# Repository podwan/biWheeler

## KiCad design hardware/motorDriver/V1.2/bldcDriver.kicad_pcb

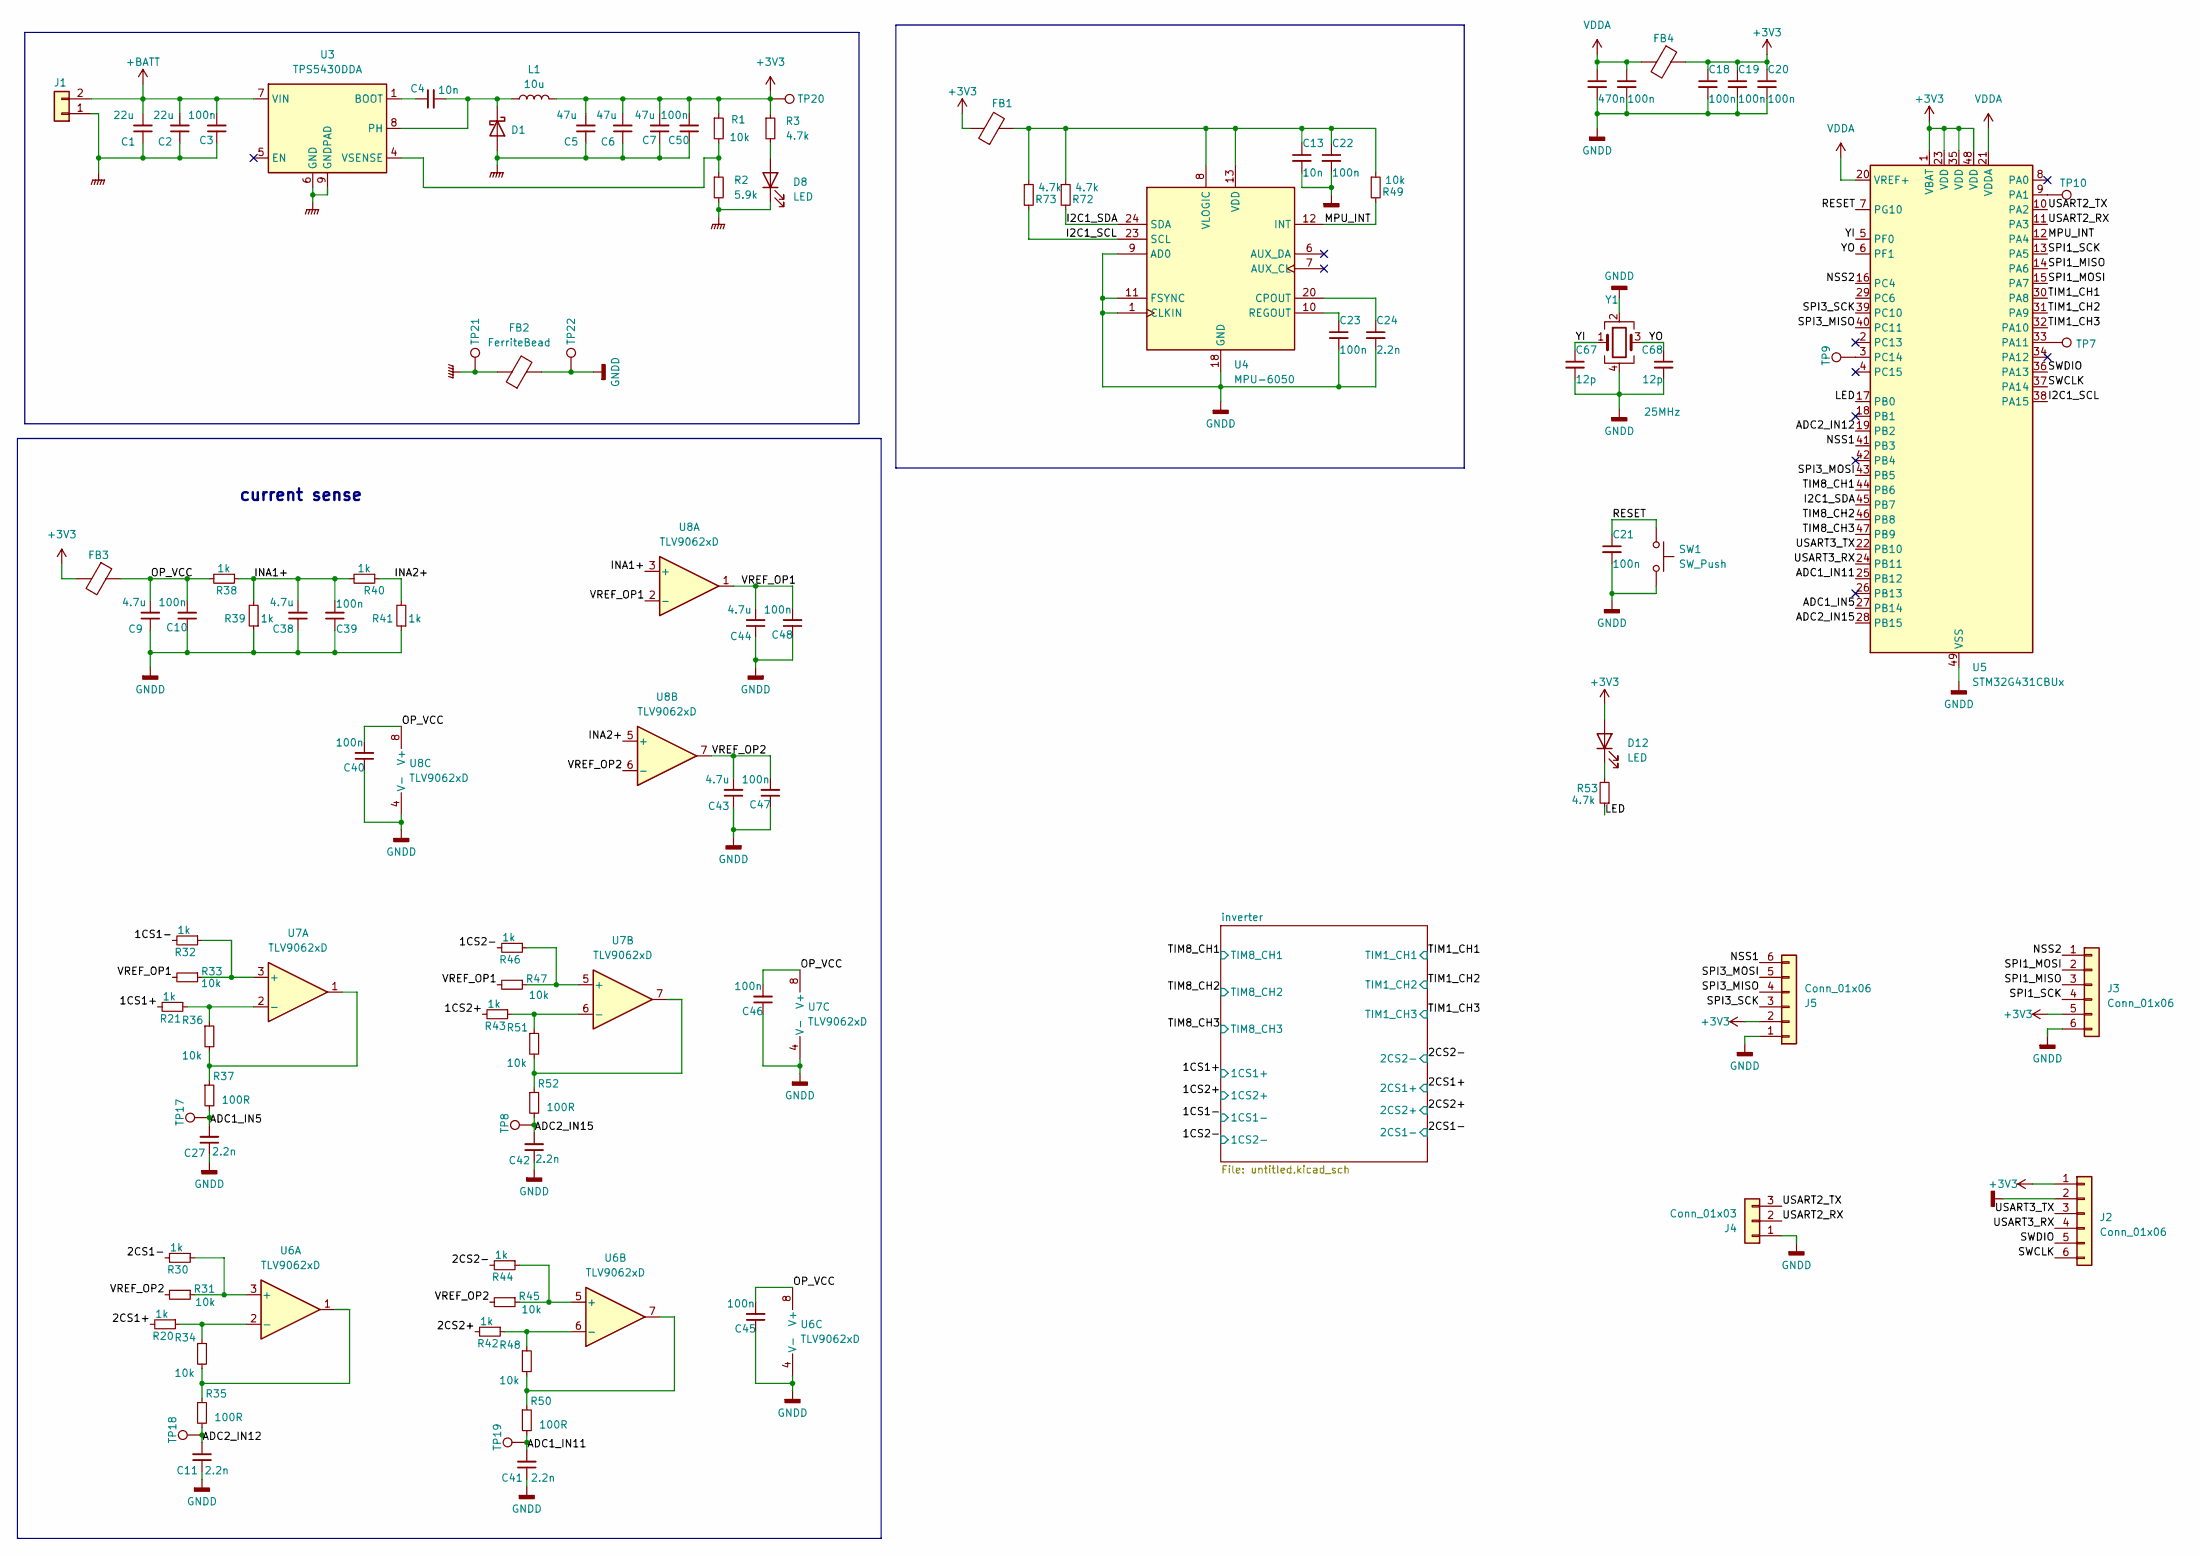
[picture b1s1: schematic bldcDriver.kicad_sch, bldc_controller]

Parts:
C1, C2: 22u; C_0805_2012Metric_Pad1.18x1.45mm_HandSolder
C3, C10, C17, C18, C19, C20, C21, C22, C23, C39, C40, C45, C46, C47, C48, C50: 100n; C_0603_1608Metric_Pad1.08x0.95mm_HandSolder
C4, C13: 10n; C_0603_1608Metric_Pad1.08x0.95mm_HandSolder
C5, C6, C7: 47u; C_1206_3216Metric_Pad1.33x1.80mm_HandSolder
C8: 470n; C_0603_1608Metric_Pad1.08x0.95mm_HandSolder
C9, C38, C43, C44: 4.7u; C_0603_1608Metric_Pad1.08x0.95mm_HandSolder
C11, C24, C27, C41, C42: 2.2n; C_0603_1608Metric_Pad1.08x0.95mm_HandSolder
C67, C68: 12p; C_0603_1608Metric_Pad1.08x0.95mm_HandSolder
D1: 1N5712UR; SMA_L4.3-W2.6-LS5.0-RD
D8: LED; LED_0603_1608Metric_Pad1.05x0.95mm_HandSolder
D12: LED; LED_0805_2012Metric_Pad1.15x1.40mm_HandSolder
FB1, FB3, FB4: FerriteBead; C_0603_1608Metric_Pad1.08x0.95mm_HandSolder
FB2: FerriteBead; R_1206_3216Metric_Pad1.30x1.75mm_HandSolder
J1: Conn_01x02; AMASS_XT30U-M_1x02_P5.0mm_Vertical
J2, J3, J5: Conn_01x06; CONN-SMD_6P-P1.00_MEGASTAR_ZX-SH1.0-6PWT
J4: Conn_01x03; CONN-SMD_3P-P1.00_WAFER-SH1.0-3PWB
L1: 10u; L_Taiyo-Yuden_NR-40xx_HandSoldering
R1, R31, R33, R34, R36, R45, R47, R48, R49, R51: 10k; R_0603_1608Metric_Pad0.98x0.95mm_HandSolder
R2: 5.9k; R_0603_1608Metric_Pad0.98x0.95mm_HandSolder
R3, R53, R72, R73: 4.7k; R_0603_1608Metric_Pad0.98x0.95mm_HandSolder
R20, R21, R30, R32, R38, R39, R40, R41, R42, R43, R44, R46: 1k; R_0603_1608Metric_Pad0.98x0.95mm_HandSolder
R35, R37, R50, R52: 100R; R_0603_1608Metric_Pad0.98x0.95mm_HandSolder
SW1: SW_Push; SW_SPST_B3U-1000P
TP7, TP8, TP9, TP10, TP17, TP18, TP19, TP20, TP21, TP22: TestPoint; TestPoint_Pad_D1.0mm
U3: TPS5430DDA; TI_SO-PowerPAD-8_ThermalVias
U4: MPU-6050; InvenSense_QFN-24_4x4mm_P0.5mm
U5: STM32G431CBUx; QFN-48-1EP_7x7mm_P0.5mm_EP5.6x5.6mm
U6, U7, U8: TLV9062xD; SOIC-8_3.9x4.9mm_P1.27mm
Y1: 25MHz; Crystal_SMD_SeikoEpson_FA238-4Pin_3.2x2.5mm

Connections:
+3V3: C5.2, C6.2, C7.2, C18.1, C19.1, C20.1, C50.2, D12.2 (A), FB1.1, FB3.2, FB4.1, J2.1, J3.5, J5.2, L1.2, R1.1, R3.1, TP20.1, U5.1 (VBAT), U5.23 (VDD), U5.35 (VDD), U5.48 (VDD)
+BATT: C1.2, C2.2, C3.2, J1.2, U3.7 (VIN); also elsewhere on the board
/1CS1+: R21.2; also elsewhere on the board
/1CS1-: R32.2; also elsewhere on the board
/1CS2+: R43.2; also elsewhere on the board
/1CS2-: R46.2; also elsewhere on the board
/2CS1+: R20.2; also elsewhere on the board
/2CS1-: R30.2; also elsewhere on the board
/2CS2+: R42.2; also elsewhere on the board
/2CS2-: R44.2; also elsewhere on the board
/ADC1_IN5: C27.2, R37.2, TP17.1, U5.27 (PB14)
/ADC1_IN11: C41.2, R50.2, TP19.1, U5.25 (PB12)
/ADC2_IN12: C11.2, R35.2, TP18.1, U5.19 (PB2)
/ADC2_IN15: C42.2, R52.2, TP8.1, U5.28 (PB15)
/I2C1_SCL: R73.2, U4.23 (SCL), U5.38 (PA15)
/I2C1_SDA: R72.2, U4.24 (SDA), U5.45 (PB7)
/INA1+: C38.2, C39.2, R38.1, R39.2, R40.2, U8.3 (+)
/INA2+: R40.1, R41.2, U8.5 (+)
/LED: R53.1, U5.17 (PB0)
/MPU_INT: R49.2, U4.12 (INT), U5.12 (PA4)
/NSS1: J5.6, U5.41 (PB3)
/NSS2: J3.1, U5.16 (PC4)
/OP_VCC: C9.2, C10.2, C40.2, C45.2, C46.2, FB3.1, R38.2, U6.8 (V+), U7.8 (V+), U8.8 (V+)
/RESET: C21.1, SW1.1, U5.7 (PG10)
/SPI1_MISO: J3.3, U5.14 (PA6)
/SPI1_MOSI: J3.2, U5.15 (PA7)
/SPI1_SCK: J3.4, U5.13 (PA5)
/SPI3_MISO: J5.4, U5.40 (PC11)
/SPI3_MOSI: J5.5, U5.43 (PB5)
/SPI3_SCK: J5.3, U5.39 (PC10)
/SWCLK: J2.6, U5.37 (PA14)
/SWDIO: J2.5, U5.36 (PA13)
/TIM1_CH1: U5.30 (PA8); also elsewhere on the board
/TIM1_CH2: U5.31 (PA9); also elsewhere on the board
/TIM1_CH3: U5.32 (PA10); also elsewhere on the board
/TIM8_CH1: U5.44 (PB6); also elsewhere on the board
/TIM8_CH2: U5.46 (PB8); also elsewhere on the board
/TIM8_CH3: U5.47 (PB9); also elsewhere on the board
/USART2_RX: J4.2, U5.11 (PA3)
/USART2_TX: J4.3, U5.10 (PA2)
/USART3_RX: J2.4, U5.24 (PB11)
/USART3_TX: J2.3, U5.22 (PB10)
/VREF_OP1: C44.2, C48.2, R33.2, R47.2, U8.1, U8.2 (-)
/VREF_OP2: C43.2, C47.2, R31.2, R45.2, U8.6 (-), U8.7
/YI: C67.1, U5.5 (PF0), Y1.1
/YO: C68.1, U5.6 (PF1), Y1.3
GNDD: C8.2, C9.1, C10.1, C11.1, C13.2, C17.2, C18.2, C19.2, C20.2, C21.2, C22.2, C23.2, C24.2, C27.1, C38.1, C39.1, C40.1, C41.1, C42.1, C43.1, C44.1, C45.1, C46.1, C47.1, C48.1, C67.2, C68.2, FB2.2, J2.2, J3.6, J4.1, J5.1, R39.1, R41.1, SW1.2, TP22.1, U4.1 (CLKIN), U4.9 (AD0), U4.11 (FSYNC), U4.18 (GND), U5.49 (VSS), U6.4 (V-), U7.4 (V-), U8.4 (V-), Y1.2, Y1.4
GNDPWR: C1.1, C2.1, C3.1, C5.1, C6.1, C7.1, C50.1, D1.2 (A), D8.1 (K), FB2.1, J1.1, R2.2, TP21.1, U3.6 (GND), U3.9 (GNDPAD); also elsewhere on the board
unnamed: C4.2, D1.1 (K), L1.1, U3.8 (PH)
unnamed: D8.2 (A), R3.2
unnamed: D12.1 (K), R53.2
unnamed: R34.2, R35.1, U6.1
unnamed: R36.2, R37.1, U7.1
unnamed: R48.2, R50.1, U6.7
unnamed: R51.2, R52.1, U7.7
unnamed: C4.1, U3.1 (BOOT)
unnamed: R1.2, R2.1, U3.4 (VSENSE)
unnamed: C24.1, U4.20 (CPOUT)
unnamed: C23.1, U4.10 (REGOUT)
unnamed: C13.1, C22.1, FB1.2, R49.1, R72.1, R73.1, U4.8 (VLOGIC), U4.13 (VDD)
unnamed: TP10.1, U5.9 (PA1)
unnamed: TP7.1, U5.33 (PA11)
unnamed: TP9.1, U5.3 (PC14)
unnamed: R30.1, R31.1, U6.3 (+)
unnamed: R20.1, R34.1, U6.2 (-)
unnamed: R44.1, R45.1, U6.5 (+)
unnamed: R42.1, R48.1, U6.6 (-)
unnamed: R32.1, R33.1, U7.3 (+)
unnamed: R21.1, R36.1, U7.2 (-)
unnamed: R46.1, R47.1, U7.5 (+)
unnamed: R43.1, R51.1, U7.6 (-)
VDDA: C8.1, C17.1, FB4.2, U5.20 (VREF+), U5.21 (VDDA)

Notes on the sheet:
current sense

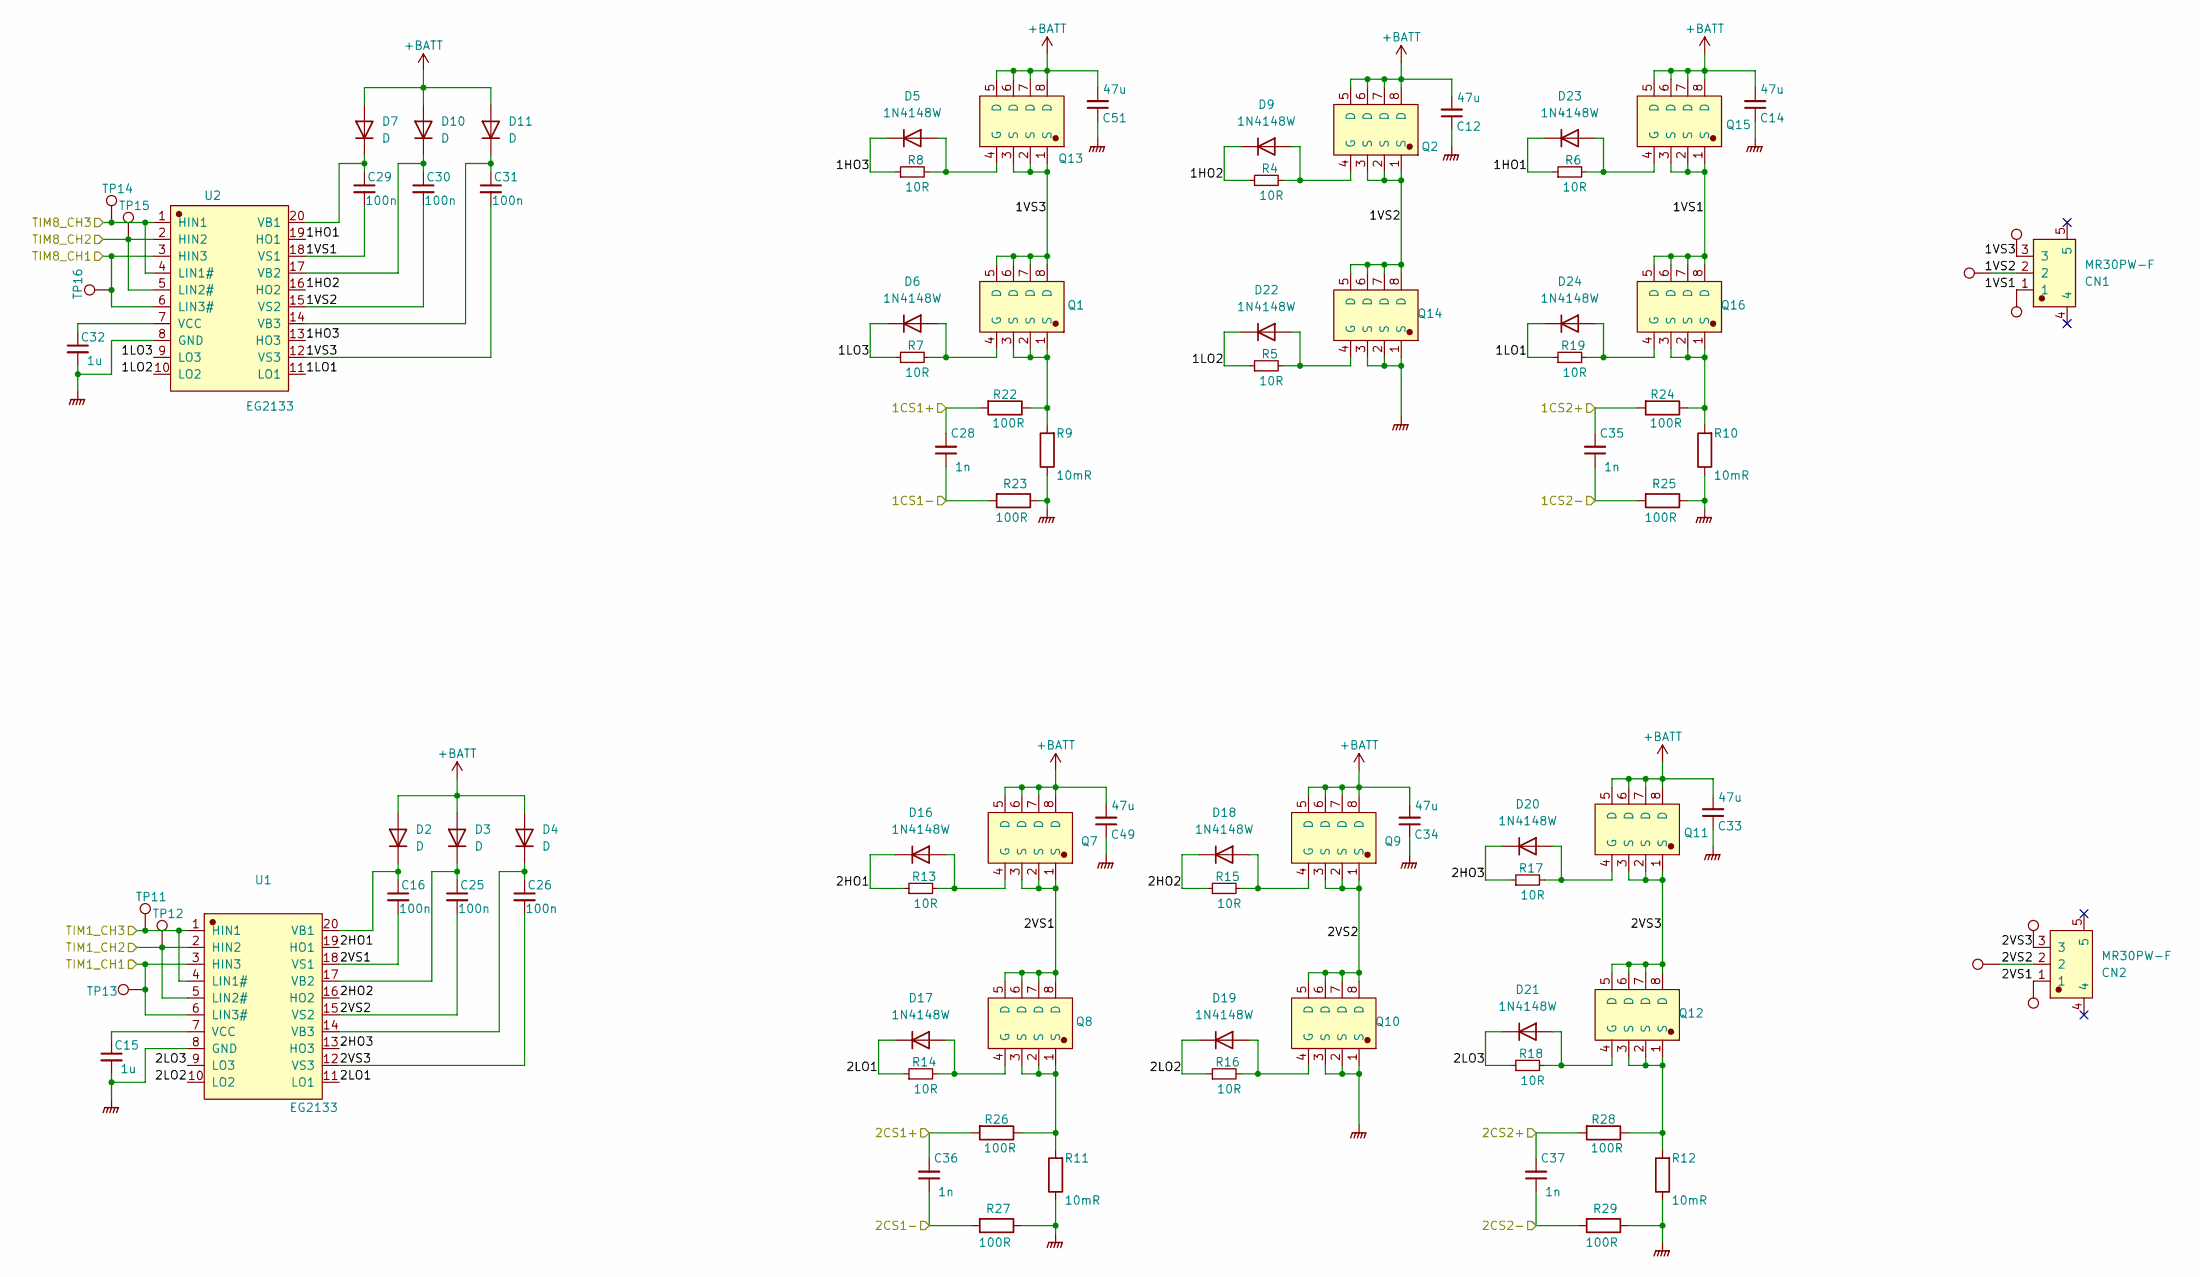
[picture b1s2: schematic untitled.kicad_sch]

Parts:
C12, C14, C33, C34, C49, C51: 47u; C_1206_3216Metric_Pad1.33x1.80mm_HandSolder
C15, C32: 1u; C_0603_1608Metric_Pad1.08x0.95mm_HandSolder
C16, C25, C26, C29, C30, C31: 100n; C_0603_1608Metric_Pad1.08x0.95mm_HandSolder
C28, C35, C36, C37: 1n; C_0603_1608Metric_Pad1.08x0.95mm_HandSolder
CN1, CN2: MR30PW-F; CONN-SMD_3P-P1.00_BX-SH1.0-3PWT
D2, D3, D4, D7, D10, D11: D; SOD-123FL_L2.7-W1.8-LS3.8-RD
D5, D6, D9, D16, D17, D18, D19, D20, D21, D22, D23, D24: 1N4148W; D_SOD-123
Q1, Q2, Q7, Q8, Q9, Q10, Q11, Q12, Q13, Q14, Q15, Q16: EMB09N03V; POWERTDFN-8_L3.1-W3.1-P0.65-LS3.3-BL
R4, R5, R6, R7, R8, R13, R14, R15, R16, R17, R18, R19: 10R; R_0603_1608Metric_Pad0.98x0.95mm_HandSolder
R9, R10, R11, R12: 10mR; R_1206_3216Metric_Pad1.30x1.75mm_HandSolder
R22, R23, R24, R25, R26, R27, R28, R29: 100R; R_0603_1608Metric_Pad0.98x0.95mm_HandSolder
TP1, TP2, TP3, TP4, TP5, TP6: TestPoint; TestPoint_Pad_1.0x1.0mm
TP11, TP12, TP13, TP14, TP15, TP16: TestPoint; TestPoint_Pad_D1.0mm
U1, U2: EG2133; eg2133

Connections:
+BATT: C12.2, C14.2, C33.2, C34.2, C49.2, C51.2, D2.2 (A), D3.2 (A), D4.2 (A), D7.2 (A), D10.2 (A), D11.2 (A), Q2.5 (D), Q2.6 (D), Q2.7 (D), Q2.8 (D), Q7.5 (D), Q7.6 (D), Q7.7 (D), Q7.8 (D), Q9.5 (D), Q9.6 (D), Q9.7 (D), Q9.8 (D), Q11.5 (D), Q11.6 (D), Q11.7 (D), Q11.8 (D), Q13.5 (D), Q13.6 (D), Q13.7 (D), Q13.8 (D), Q15.5 (D), Q15.6 (D), Q15.7 (D), Q15.8 (D); also elsewhere on the board
/1CS1+: C28.2, R22.2; also elsewhere on the board
/1CS1-: C28.1, R23.2; also elsewhere on the board
/1CS2+: C35.2, R24.2; also elsewhere on the board
/1CS2-: C35.1, R25.2; also elsewhere on the board
/2CS1+: C36.2, R26.2; also elsewhere on the board
/2CS1-: C36.1, R27.2; also elsewhere on the board
/2CS2+: C37.2, R28.2; also elsewhere on the board
/2CS2-: C37.1, R29.2; also elsewhere on the board
/TIM1_CH1: TP13.1, U1.3 (HIN3), U1.6 (LIN3#); also elsewhere on the board
/TIM1_CH2: TP12.1, U1.2 (HIN2), U1.5 (LIN2#); also elsewhere on the board
/TIM1_CH3: TP11.1, U1.1 (HIN1), U1.4 (LIN1#); also elsewhere on the board
/TIM8_CH1: TP16.1, U2.3 (HIN3), U2.6 (LIN3#); also elsewhere on the board
/TIM8_CH2: TP15.1, U2.2 (HIN2), U2.5 (LIN2#); also elsewhere on the board
/TIM8_CH3: TP14.1, U2.1 (HIN1), U2.4 (LIN1#); also elsewhere on the board
/inverter/1HO1: D23.1 (K), R6.1, U2.19 (HO1)
/inverter/1HO2: D9.1 (K), R4.1, U2.16 (HO2)
/inverter/1HO3: D5.1 (K), R8.1, U2.13 (HO3)
/inverter/1LO1: D24.1 (K), R19.1, U2.11 (LO1)
/inverter/1LO2: D22.1 (K), R5.1, U2.10 (LO2)
/inverter/1LO3: D6.1 (K), R7.1, U2.9 (LO3)
/inverter/1VS1: C29.2, CN1.1, Q15.1 (S), Q15.2 (S), Q15.3 (S), Q16.5 (D), Q16.6 (D), Q16.7 (D), Q16.8 (D), TP3.1, U2.18 (VS1)
/inverter/1VS2: C30.2, CN1.2, Q2.1 (S), Q2.2 (S), Q2.3 (S), Q14.5 (D), Q14.6 (D), Q14.7 (D), Q14.8 (D), TP2.1, U2.15 (VS2)
/inverter/1VS3: C31.2, CN1.3, Q1.5 (D), Q1.6 (D), Q1.7 (D), Q1.8 (D), Q13.1 (S), Q13.2 (S), Q13.3 (S), TP1.1, U2.12 (VS3)
/inverter/2HO1: D16.1 (K), R13.1, U1.19 (HO1)
/inverter/2HO2: D18.1 (K), R15.1, U1.16 (HO2)
/inverter/2HO3: D20.1 (K), R17.1, U1.13 (HO3)
/inverter/2LO1: D17.1 (K), R14.1, U1.11 (LO1)
/inverter/2LO2: D19.1 (K), R16.1, U1.10 (LO2)
/inverter/2LO3: D21.1 (K), R18.1, U1.9 (LO3)
/inverter/2VS1: C16.2, CN2.1, Q7.1 (S), Q7.2 (S), Q7.3 (S), Q8.5 (D), Q8.6 (D), Q8.7 (D), Q8.8 (D), TP6.1, U1.18 (VS1)
/inverter/2VS2: C25.2, CN2.2, Q9.1 (S), Q9.2 (S), Q9.3 (S), Q10.5 (D), Q10.6 (D), Q10.7 (D), Q10.8 (D), TP5.1, U1.15 (VS2)
/inverter/2VS3: C26.2, CN2.3, Q11.1 (S), Q11.2 (S), Q11.3 (S), Q12.5 (D), Q12.6 (D), Q12.7 (D), Q12.8 (D), TP4.1, U1.12 (VS3)
GNDPWR: C12.1, C14.1, C15.2, C32.2, C33.1, C34.1, C49.1, C51.1, Q10.1 (S), Q10.2 (S), Q10.3 (S), Q14.1 (S), Q14.2 (S), Q14.3 (S), R9.1, R10.1, R11.1, R12.1, R23.1, R25.1, R27.1, R29.1, U1.8 (GND), U2.8 (GND); also elsewhere on the board
unnamed: C16.1, D2.1 (K), U1.20 (VB1)
unnamed: C25.1, D3.1 (K), U1.17 (VB2)
unnamed: C26.1, D4.1 (K), U1.14 (VB3)
unnamed: D5.2 (A), Q13.4 (G), R8.2
unnamed: D6.2 (A), Q1.4 (G), R7.2
unnamed: C29.1, D7.1 (K), U2.20 (VB1)
unnamed: D9.2 (A), Q2.4 (G), R4.2
unnamed: C30.1, D10.1 (K), U2.17 (VB2)
unnamed: C31.1, D11.1 (K), U2.14 (VB3)
unnamed: D16.2 (A), Q7.4 (G), R13.2
unnamed: D17.2 (A), Q8.4 (G), R14.2
unnamed: D18.2 (A), Q9.4 (G), R15.2
unnamed: D19.2 (A), Q10.4 (G), R16.2
unnamed: D20.2 (A), Q11.4 (G), R17.2
unnamed: D21.2 (A), Q12.4 (G), R18.2
unnamed: D22.2 (A), Q14.4 (G), R5.2
unnamed: D23.2 (A), Q15.4 (G), R6.2
unnamed: D24.2 (A), Q16.4 (G), R19.2
unnamed: Q1.1 (S), Q1.2 (S), Q1.3 (S), R9.2, R22.1
unnamed: Q8.1 (S), Q8.2 (S), Q8.3 (S), R11.2, R26.1
unnamed: Q12.1 (S), Q12.2 (S), Q12.3 (S), R12.2, R28.1
unnamed: Q16.1 (S), Q16.2 (S), Q16.3 (S), R10.2, R24.1
unnamed: C15.1, U1.7 (VCC)
unnamed: C32.1, U2.7 (VCC)

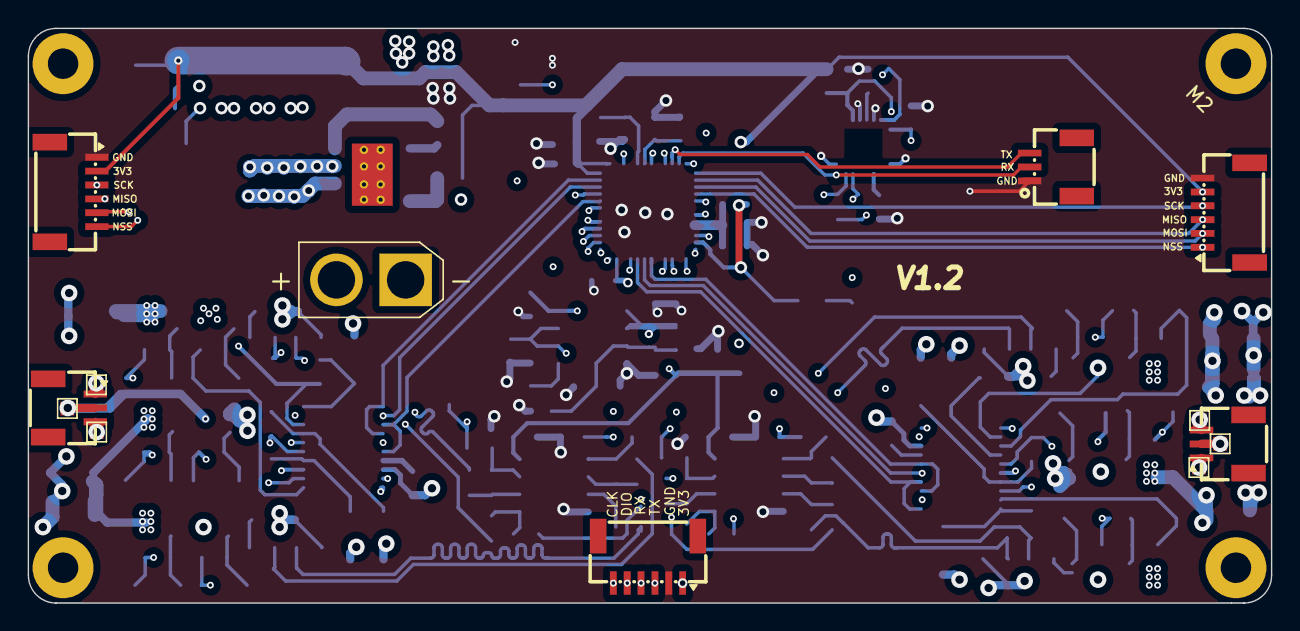
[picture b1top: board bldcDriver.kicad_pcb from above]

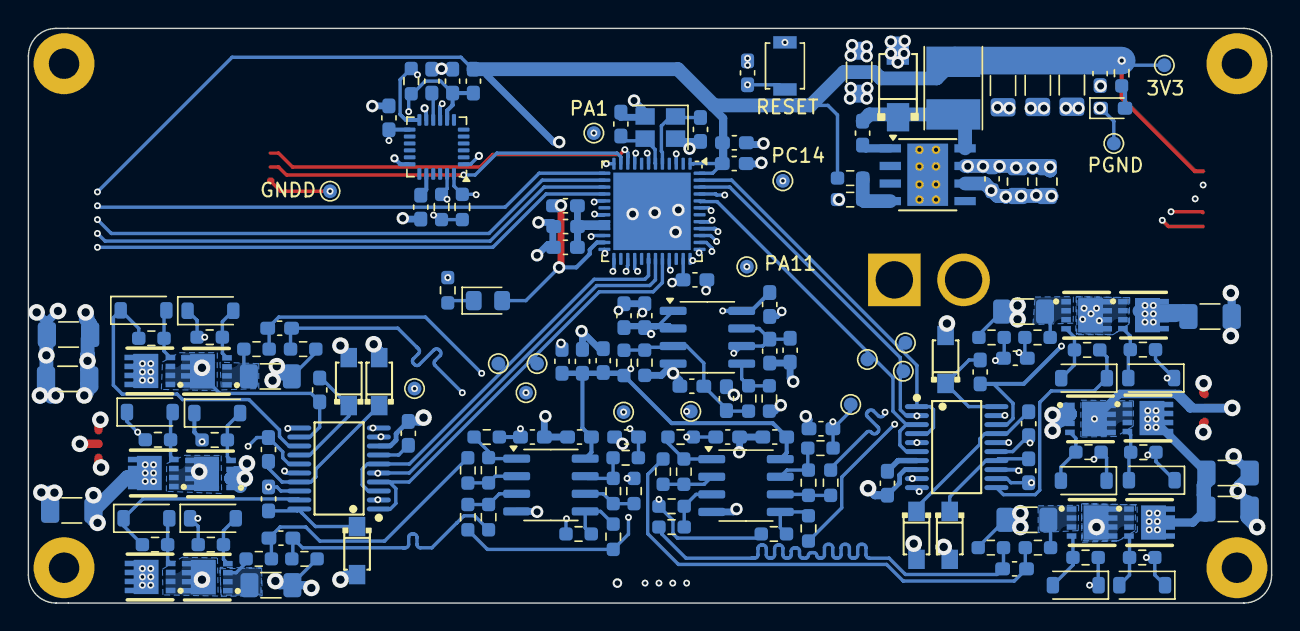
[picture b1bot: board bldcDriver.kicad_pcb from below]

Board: 4 copper layers, 89.8 x 41.5 mm, 185 parts (172 on the bottom side), 114 nets.

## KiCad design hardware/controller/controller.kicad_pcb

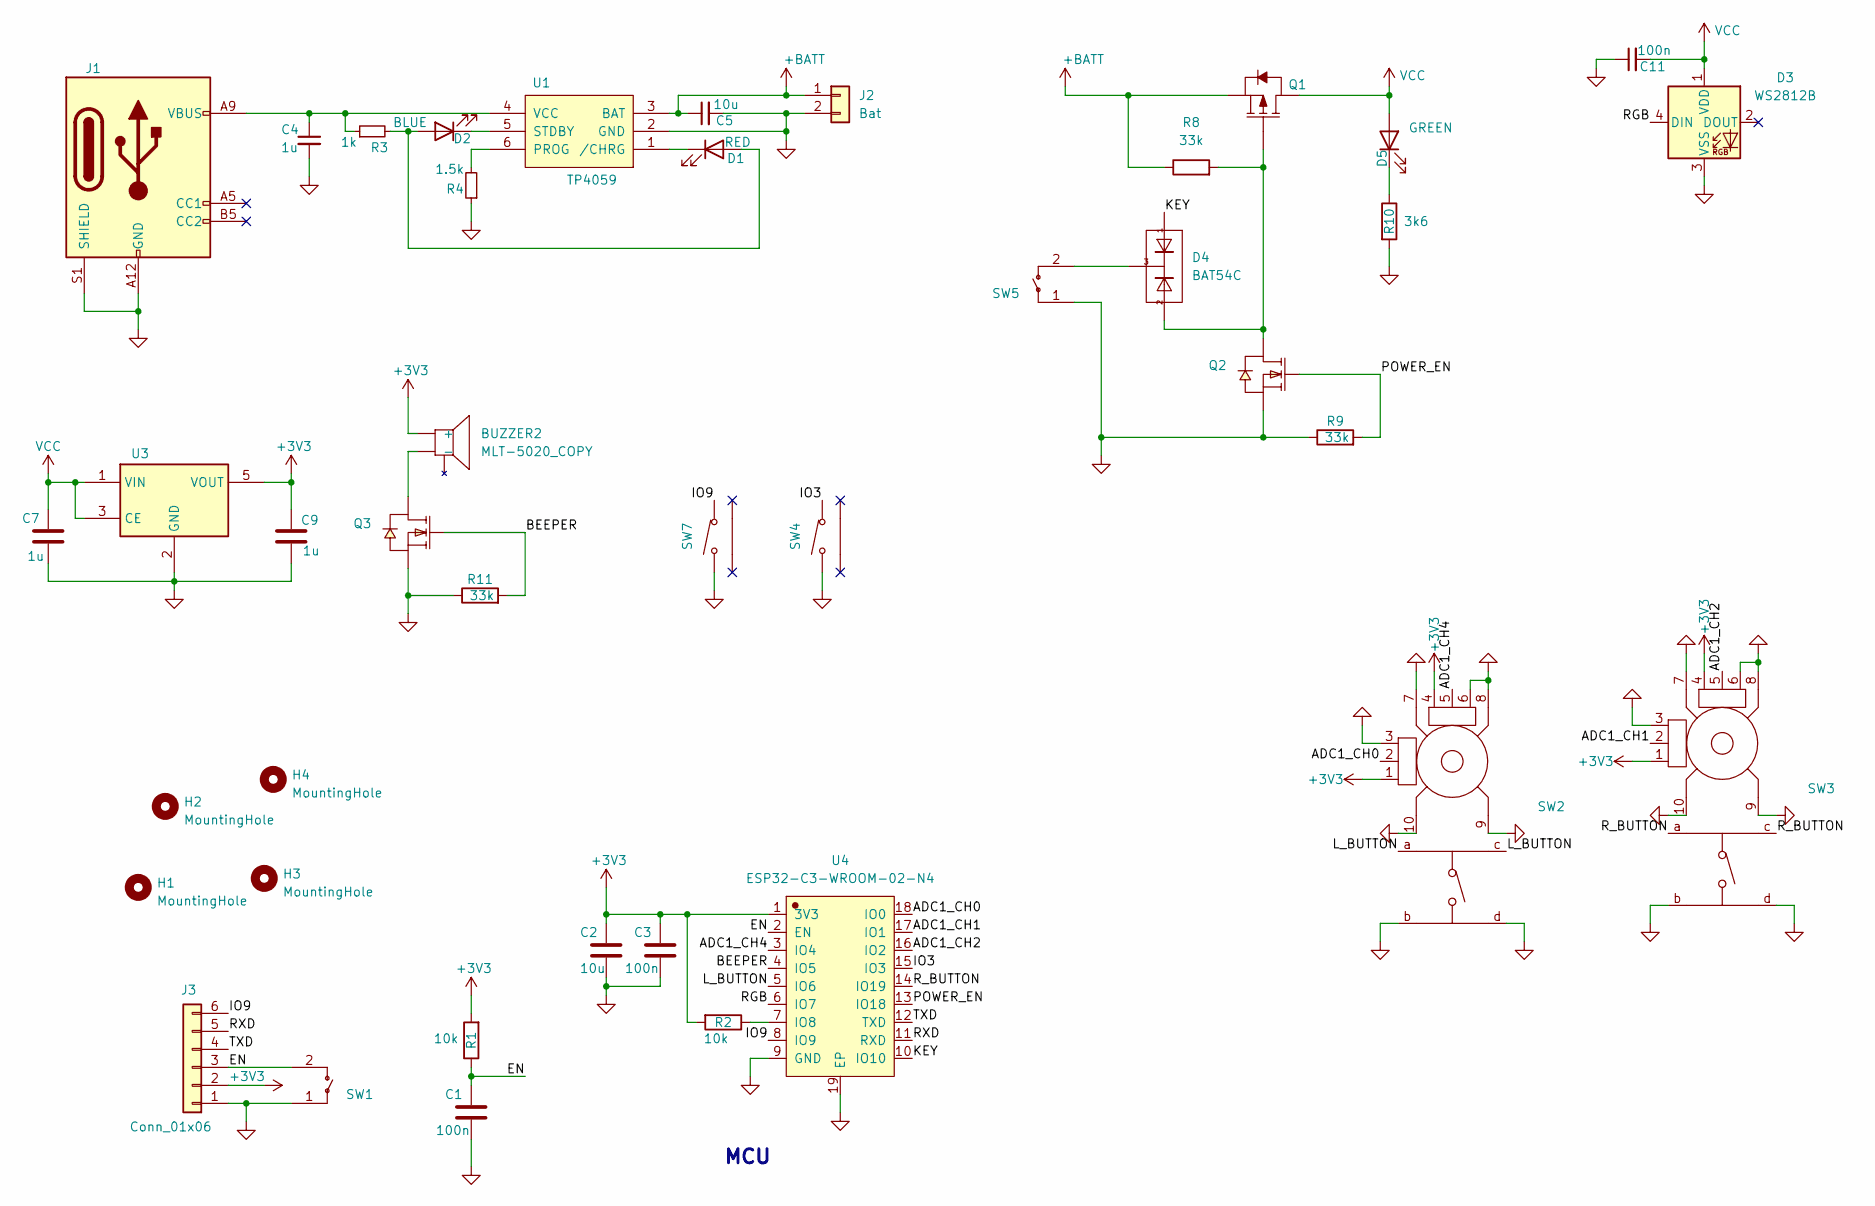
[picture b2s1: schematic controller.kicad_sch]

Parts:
BUZZER2: MLT-5020_COPY; BUZ-SMD_L5.0-W5.5-P4.60
C1, C3, C11: 100n; C_0603_1608Metric_Pad1.08x0.95mm_HandSolder
C2, C5: 10u; C_0805_2012Metric_Pad1.18x1.45mm_HandSolder
C4, C7, C9: 1u; C_0603_1608Metric_Pad1.08x0.95mm_HandSolder
D1: RED; LED_0603_1608Metric_Pad1.05x0.95mm_HandSolder
D2: BLUE; LED_0603_1608Metric_Pad1.05x0.95mm_HandSolder
D3: WS2812B; LED_WS2812B_PLCC4_5.0x5.0mm_P3.2mm
D4: BAT54C; SOT-23
D5: GREEN; LED_0603_1608Metric_Pad1.05x0.95mm_HandSolder
H1, H2, H3, H4: MountingHole; MountingHole_2.2mm_M2_Pad
J1: USB_C_Receptacle_PowerOnly_6P; USB-C-SMD_HX-TYPE-C-6PIN
J2: Bat; CONN-SMD_2P-P2.54-XH2.54-WT
J3: Conn_01x06; CONN-SMD_6P-P1.00_XYECONN_XY-SH1.0-6A61
Q1: AO3401; SOT-23
Q2, Q3: AllPower__AP2300; SOT-23
R1, R2: 10k; R_0603_1608Metric_Pad0.98x0.95mm_HandSolder
R3: 1k; R_0603_1608Metric_Pad0.98x0.95mm_HandSolder
R4: 1.5k; R_0603_1608Metric_Pad0.98x0.95mm_HandSolder
R8, R9, R11: 33k; R_0603_1608Metric_Pad0.98x0.95mm_HandSolder
R10: 3k6; R_0603_1608Metric_Pad0.98x0.95mm_HandSolder
SW1, SW5: TS-1199A-B-B; SW-SMD_L6.0-W6.0-P6.00-LS6.6
SW2, SW3: RKJXV1224005; SW-TH_RKJXV1224005
SW4, SW7: TC-1102N-C-AS-B; SW-TH_TC-1102N-C-AS-B
U1: TP4059; SOT-23-6_L2.9-W1.6-P0.95-LS2.8-BR
U3: XC6220B331MR; SOT-23-5
U4: ESP32-C3-WROOM-02-N4; ESP32-C3-WROOM-02

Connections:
+3V3: BUZZER2.1 (+), C2.1, C3.1, C9.1, J3.2, R1.2, R2.2, SW2.1 (B), SW2.4 (A), SW3.1 (B), SW3.4 (A), U3.5 (VOUT), U4.1 (3V3)
+BATT: C5.1, J2.1, Q1.2 (S), R8.1, U1.3 (BAT)
/ADC1_CH0: SW2.2 (DTA), U4.18 (IO0)
/ADC1_CH1: SW3.2 (DTA), U4.17 (IO1)
/ADC1_CH2: SW3.5 (DTA), U4.16 (IO2)
/ADC1_CH4: SW2.5 (DTA), U4.3 (IO4)
/BEEPER: Q3.1 (G), R11.2, U4.4 (IO5)
/EN: C1.1, J3.3, R1.1, SW1.2, U4.2 (EN)
/IO3: SW4.2, U4.15 (IO3)
/IO9: J3.6, SW7.2, U4.8 (IO9)
/KEY: D4.1 (A), U4.10 (IO10)
/L_BUTTON: SW2.a, SW2.c, U4.5 (IO6)
/POWER_EN: Q2.1 (G), R9.2, U4.13 (IO18)
/RGB: D3.4 (DIN), U4.6 (IO7)
/RXD: J3.5, U4.11 (RXD)
/R_BUTTON: SW3.a, SW3.c, U4.14 (IO19)
/TXD: J3.4, U4.12 (TXD)
GND: C1.2, C2.2, C3.2, C4.2, C5.2, C7.2, C9.2, C11.1, D3.3 (VSS), J1.A12 (GND), J1.B12 (GND), J1.S1 (SHIELD), J2.2, J3.1, Q2.2 (S), Q3.2 (S), R4.1, R9.1, R10.2, R11.1, SW1.1, SW2.3 (A), SW2.6 (B), SW2.7 (GND), SW2.8 (GND), SW2.9 (GND), SW2.10 (GND), SW2.b, SW2.d, SW3.3 (A), SW3.6 (B), SW3.7 (GND), SW3.8 (GND), SW3.9 (GND), SW3.10 (GND), SW3.b, SW3.d, SW4.1, SW5.1, SW7.1, U1.2 (GND), U3.2 (GND), U4.9 (GND), U4.19 (EP)
unnamed: BUZZER2.2 (-), Q3.3 (D)
unnamed: D1.2 (A), D2.2 (A), R3.2
unnamed: D1.1 (K), U1.1 (/CHRG)
unnamed: D2.1 (K), U1.5 (STDBY)
unnamed: D4.3 (C), SW5.2
unnamed: D5.1 (K), R10.1
unnamed: D4.2 (A), Q1.1 (G), Q2.3 (D), R8.2
unnamed: R4.2, U1.6 (PROG)
unnamed: C4.1, J1.A9 (VBUS), J1.B9 (VBUS), R3.1, U1.4 (VCC)
unnamed: R2.1, U4.7 (IO8)
VCC: C7.1, C11.2, D3.1 (VDD), D5.2 (A), Q1.3 (D), U3.1 (VIN), U3.3 (CE)

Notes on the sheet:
MCU

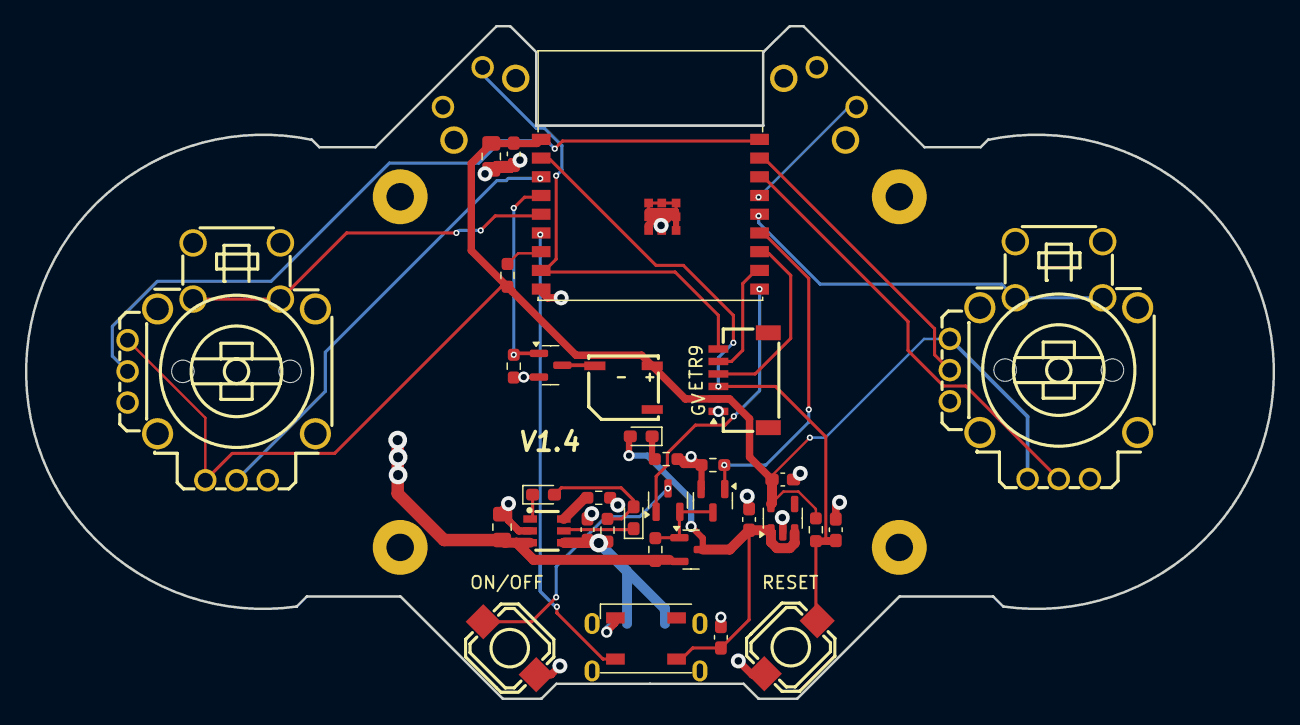
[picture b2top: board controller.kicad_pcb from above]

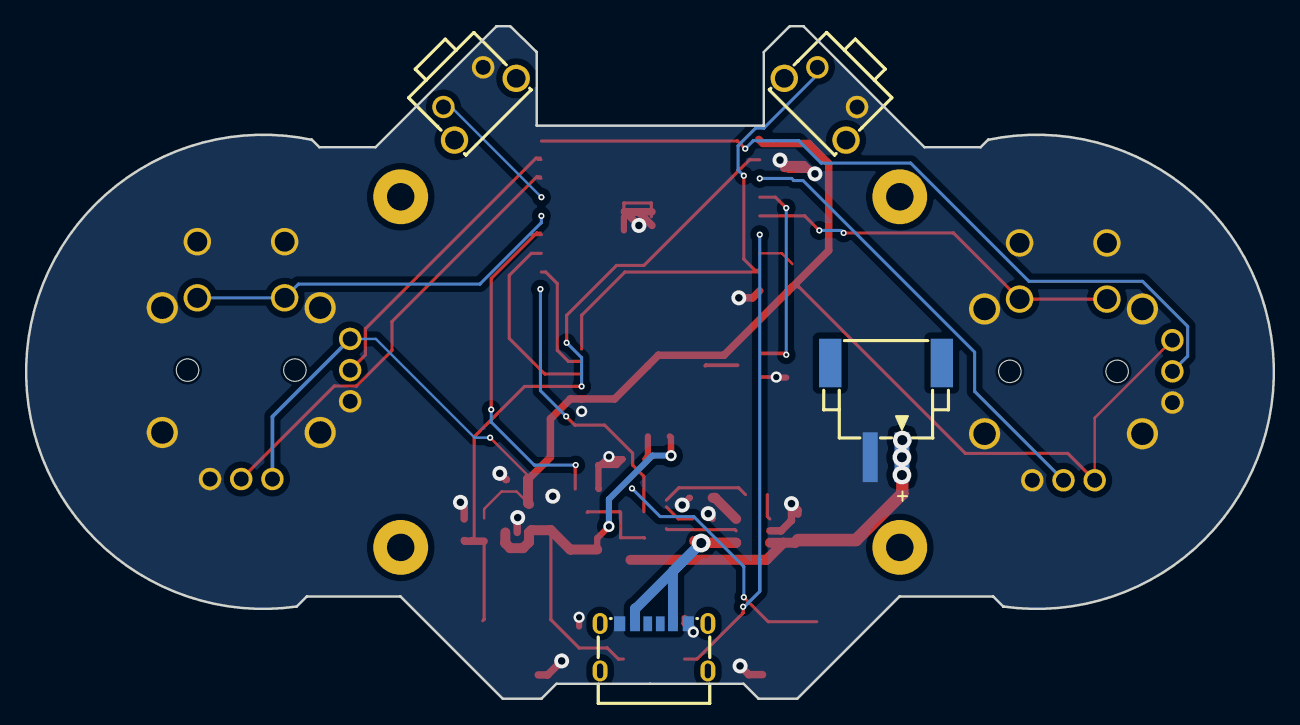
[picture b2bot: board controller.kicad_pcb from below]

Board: 2 copper layers, 100.0 x 53.9 mm, 41 parts (4 on the bottom side), 29 nets.
